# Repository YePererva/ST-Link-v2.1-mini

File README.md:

# ST-Link v2.1 - mini

** Status ** : Unfinished and deprecated due to obtaining the [STLink V3 mini](https://www.st.com/en/development-tools/stlink-v3mini.html)

The idea of this project came, when I broke my [NUCLEO-L432KC](https://www.st.com/content/st_com/en/products/evaluation-tools/product-evaluation-tools/mcu-mpu-eval-tools/stm32-mcu-mpu-eval-tools/stm32-nucleo-boards/nucleo-l432kc.html) board and thought if I can cannibalize the leftovers of it and make a replacement PCB, where I can transplant the microcontroller and keep using the chip from Nucleo board as a dedicated STLink programmer.

This repository has no purpose or instructions for hacking the firmware or any other part of STLink!

Although, the schematic of original [NUCLEO-L432KC](https://www.st.com/resource/en/data_brief/nucleo-l432kc.pdf) and its STLink part is available [on STMicroelectronics website](https://www.st.com/resource/en/schematic_pack/nucleo-32pins_sch.zip) it has few points that I don't like:
- it uses USB-micro, while USB type C seems to be more appropriate
- STMicroelectronics introduced the `STCD-14` connector for STM32 programming (via SWD + VCP). It would be nice to have it
- official firmware allows to switch device between programming the STM32 and STM8 microcontrollers
- the [Black Magic Probe](https://github.com/blacksphere/blackmagic/wiki) is another popular programming / debugging tool and have a [firmware](https://github.com/blacksphere/blackmagic/tree/master/src/platforms/stlink), compatible with STM32F103CxT6 microcontroller. It may be reasonable to have a programming interface to convert this DIY STLink into BMP later in future.
- can't power-up the target microcontroller from STLink.

## What is inside of repository
- `datasheets`: \
  datasheets for microcontroller, USB type Connector, etc.
- `project files`:
  - `simplified`: \
    simplified version of STLink without EDS protection of either USB or SWD / SWIM / VCP
  - `protected`: \
    version with EDS protection
  - `STDC14-adapters`: \
    The STLink V3 mini can't be connected directly to devboards alike BluePill, etc. due to different connector pinout and size. Here are 2 connectors for STDC14 : as breadboard breakout board and as plug-&-play connector to SWD interface on BluePill board.
- `references`: \
    references on stuff like pinout of programming interfaces, STLinks made by other people, etc.

### Similar projects

- https://github.com/MartinD-CZ/ST-Link-V21-clone

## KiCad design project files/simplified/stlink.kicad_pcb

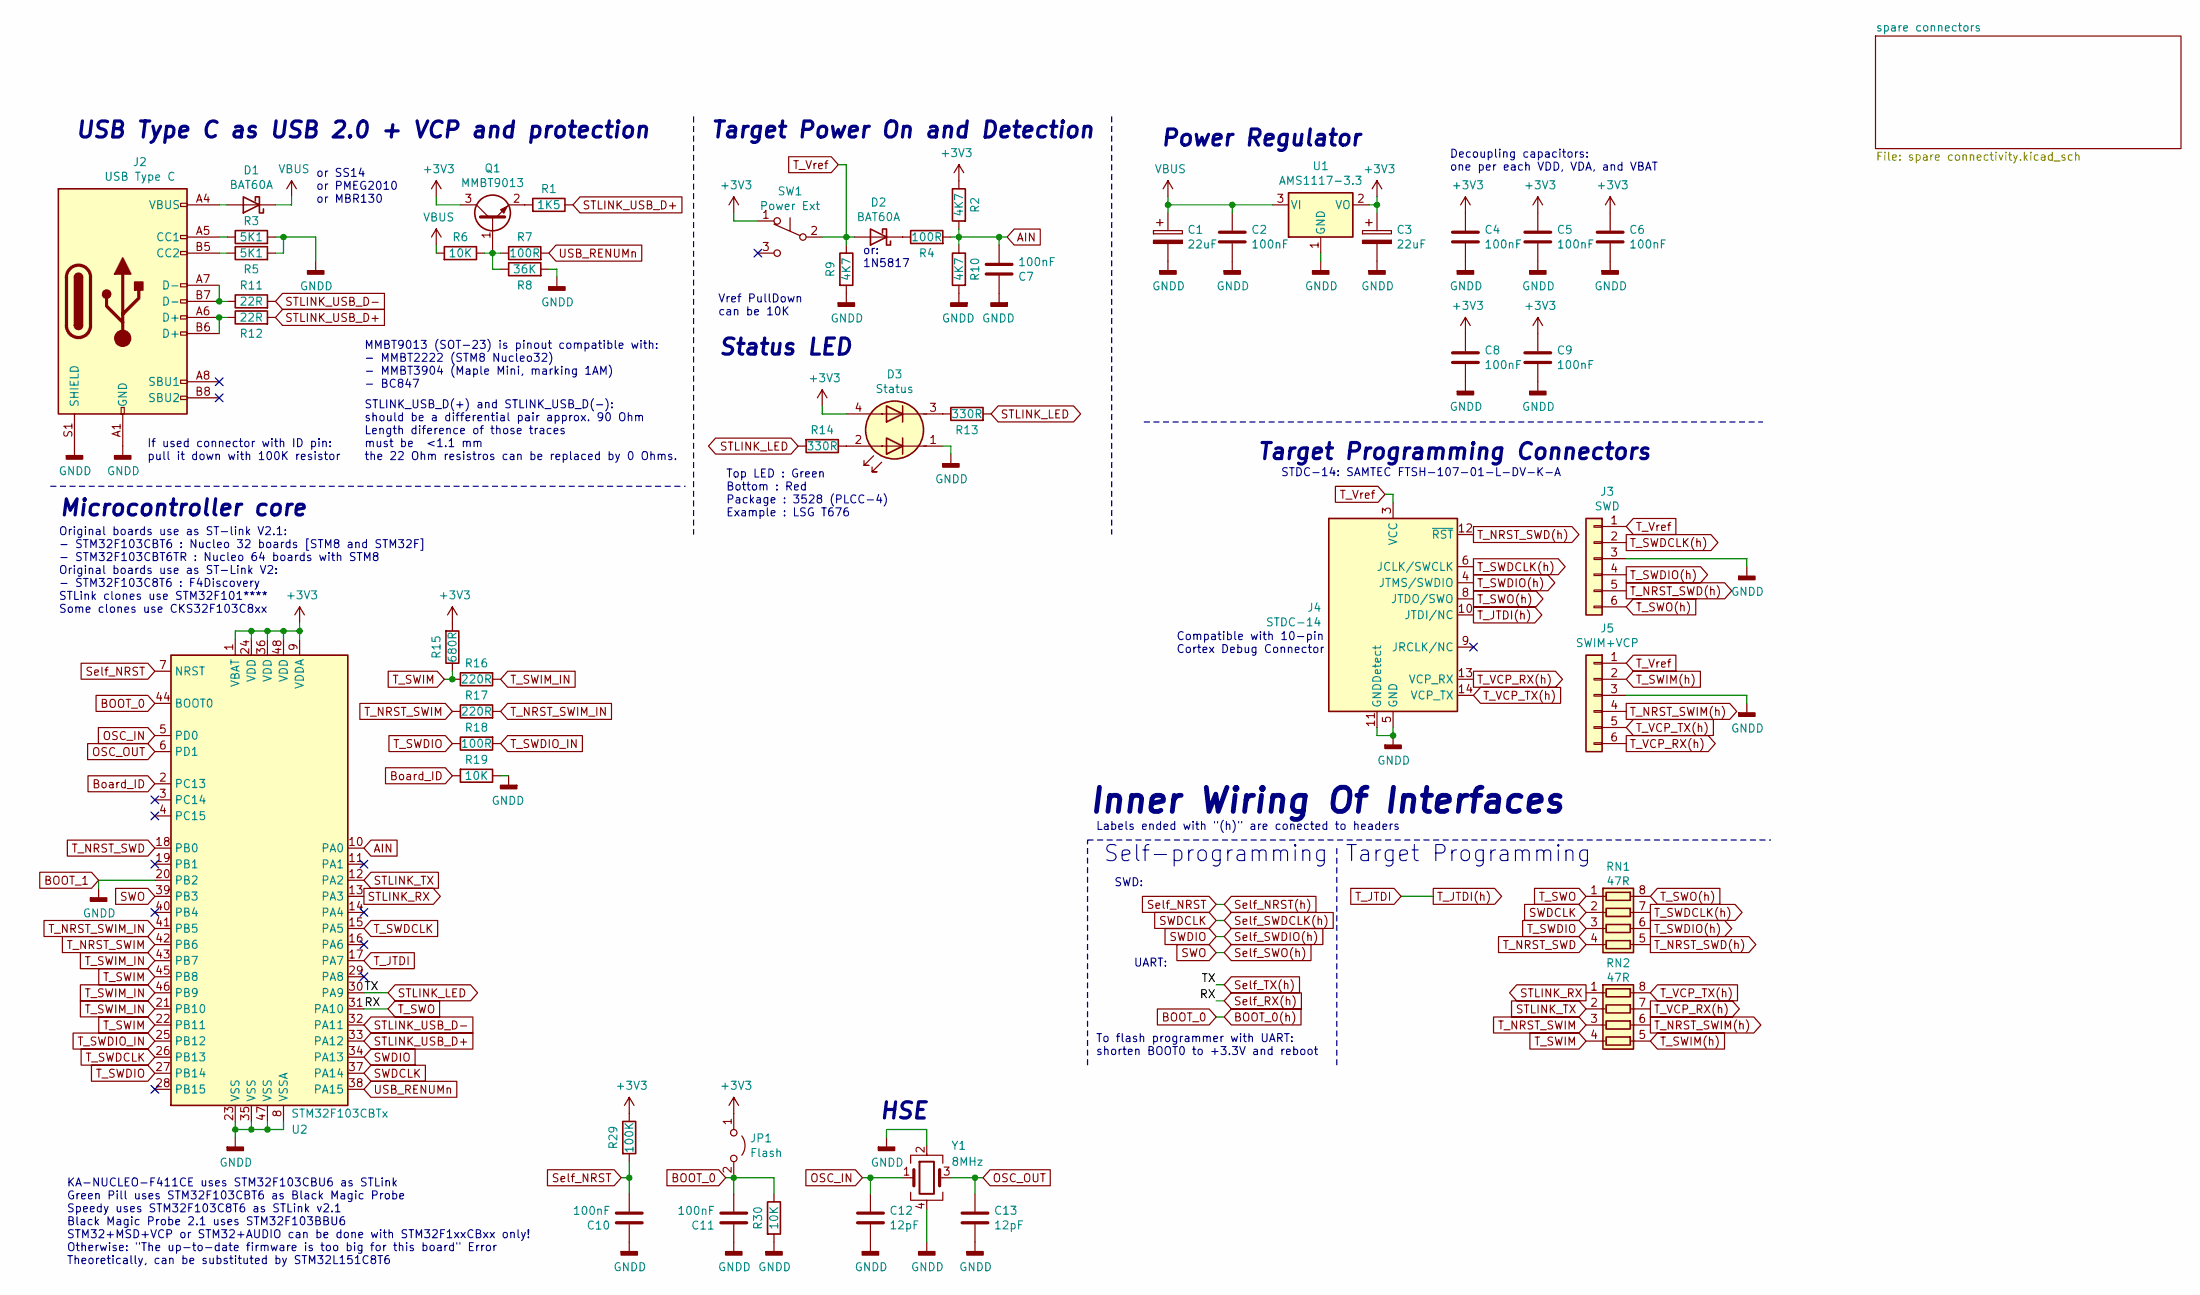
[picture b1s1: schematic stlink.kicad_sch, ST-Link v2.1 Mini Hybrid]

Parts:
C1, C3: 22uF; CP_EIA-7343-30_AVX-N
C2, C4, C5, C6, C7, C8, C9, C10, C11: 100nF; C_0603_1608Metric
C12, C13: 12pF; C_0603_1608Metric
D1, D2: BAT60A; D_SOD-323
D3: Status; LED_Avago_PLCC4_3.2x2.8mm_CW
J2: USB Type C; USB_C_Receptacle_Palconn_UTC16-G
J3: SWD; PinHeader_1x06_P2.54mm_Vertical
J4: STDC-14; PinHeader_2x07_P1.27mm_Vertical_SMD
J5: SWIM+VCP; PinHeader_1x06_P2.54mm_Vertical
JP1: Flash; PinSocket_2x01_P1.27mm_Vertical
Q1: MMBT9013; SOT-23
R1: 1K5; R_0603_1608Metric
R2, R9, R10: 4K7; R_0603_1608Metric
R3, R5: 5K1; R_0603_1608Metric
R4, R7, R18: 100R; R_0603_1608Metric
R6, R19, R30: 10K; R_0603_1608Metric
R8: 36K; R_0603_1608Metric
R11, R12: 22R; R_0603_1608Metric
R13, R14: 330R; R_0603_1608Metric
R15: 680R; R_0603_1608Metric
R16, R17: 220R; R_0603_1608Metric
R29: 100K; R_0603_1608Metric
RN1, RN2: 47R
SW1: Power Ext
U1: AMS1117-3.3; SOT-223-3_TabPin2
U2: STM32F103CBTx; LQFP-48_7x7mm_P0.5mm
Y1: 8MHz; Crystal_SMD_Abracon_ABM8G-4Pin_3.2x2.5mm

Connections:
AIN: C7.2, R2.2, R4.2, R10.1, U2.10 (PA0); also elsewhere on the board
BOOT_0: C11.2, JP1.2 (B), R30.1, U2.44 (BOOT0); also elsewhere on the board
BOOT_1: C1.2, C2.2, C3.2, C4.2, C5.2, C6.2, C7.1, C8.2, C9.2, C10.1, C11.1, C12.2, C13.2, D3.1 (A1), J2.A1 (GND), J2.A12 (GND), J2.B1 (GND), J2.B12 (GND), J2.S1 (SHIELD), J3.3, J4.5 (GND), J4.7 (GND), J4.11 (GNDDetect), J5.3, R3.2, R5.2, R8.2, R9.2, R10.2, R19.1, R30.2, U1.1 (GND), U2.8 (VSSA), U2.20 (PB2), U2.23 (VSS), U2.35 (VSS), U2.47 (VSS), Y1.2, Y1.4; also elsewhere on the board
Board_ID: R19.2, U2.2 (PC13); also elsewhere on the board
unnamed: D1.2 (A), J2.A4 (VBUS), J2.A9 (VBUS), J2.B4 (VBUS), J2.B9 (VBUS)
unnamed: D2.1 (K), R4.1
unnamed: D3.2 (K1), R14.1
unnamed: D3.3 (A2), R13.1
unnamed: J2.A5 (CC1), R3.1
unnamed: J2.A6 (D+), J2.B6 (D+), R12.1
unnamed: J2.A7 (D-), J2.B7 (D-), R11.1
unnamed: J2.B5 (CC2), R5.1
unnamed: Q1.1 (B), R6.1, R7.1, R8.1
unnamed: Q1.2 (E), R1.2
OSC_IN: C12.1, U2.5 (PD0), Y1.1; also elsewhere on the board
OSC_OUT: C13.1, U2.6 (PD1), Y1.3; also elsewhere on the board
STLINK_LED: R13.2, R14.2, U2.30 (PA9); also elsewhere on the board
STLINK_RX: RN2.1 (R1.1), U2.13 (PA3); also elsewhere on the board
STLINK_TX: RN2.2 (R2.1), U2.12 (PA2); also elsewhere on the board
STLINK_USB_D+: R1.1, R12.2, U2.33 (PA12); also elsewhere on the board
STLINK_USB_D-: R11.2, U2.32 (PA11); also elsewhere on the board
SWDCLK: RN1.2 (R2.1), U2.37 (PA14); also elsewhere on the board
SWDIO: U2.34 (PA13); also elsewhere on the board
SWO: U2.39 (PB3); also elsewhere on the board
Self_NRST: C10.2, R29.2, U2.7 (NRST); also elsewhere on the board
Self_RX(h): RN1.1 (R1.1), U2.31 (PA10); also elsewhere on the board
T_JTDI: J4.10 (JTDI/NC), U2.17 (PA7); also elsewhere on the board
T_NRST_SWD: RN1.4 (R4.1), U2.18 (PB0); also elsewhere on the board
T_NRST_SWD(h): J3.5, J4.12 (~RST), RN1.5 (R4.2)
T_NRST_SWIM: R17.1, RN2.3 (R3.1), U2.42 (PB6); also elsewhere on the board
T_NRST_SWIM(h): J5.4, RN2.6 (R3.2)
T_NRST_SWIM_IN: R17.2, U2.41 (PB5); also elsewhere on the board
T_SWDCLK: U2.15 (PA5), U2.26 (PB13); also elsewhere on the board
T_SWDCLK(h): J3.2, J4.6 (JCLK/SWCLK), RN1.7 (R2.2)
T_SWDIO: R18.1, RN1.3 (R3.1), U2.27 (PB14); also elsewhere on the board
T_SWDIO(h): J3.4, J4.4 (JTMS/SWDIO), RN1.6 (R3.2)
T_SWDIO_IN: R18.2, U2.25 (PB12); also elsewhere on the board
T_SWIM: R15.1, R16.1, RN2.4 (R4.1), U2.22 (PB11), U2.45 (PB8); also elsewhere on the board
T_SWIM(h): J5.2, RN2.5 (R4.2)
T_SWIM_IN: R16.2, U2.21 (PB10), U2.43 (PB7), U2.46 (PB9); also elsewhere on the board
T_SWO(h): J3.6, J4.8 (JTDO/SWO), RN1.8 (R1.2)
T_VCP_RX(h): J4.13 (VCP_RX), J5.6, RN2.7 (R2.2)
T_VCP_TX(h): J4.14 (VCP_TX), J5.5, RN2.8 (R1.2)
T_Vref: D2.2 (A), J3.1, J4.3 (VCC), J5.1, R9.1, SW1.2 (B)
USB_RENUMn: R7.2, U2.38 (PA15); also elsewhere on the board
VBUS: C1.1, C2.1, D1.1 (K), R6.2, U1.3 (VI)

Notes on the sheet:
Microcontroller core
Original boards use as ST-link V2.1: - STM32F103CBT6 : Nucleo 32 boards [STM8 and STM32F] - STM32F103CBT6TR : Nucleo 64 boards with STM8 Original boards use as ST-Link V2: - STM32F103C8T6 : F4Discovery STLink clones use STM32F101**** Some clones use CKS32F103C8xx
KA-NUCLEO-F411CE uses STM32F103CBU6 as STLink Green Pill uses STM32F103CBT6 as Black Magic Probe Speedy uses STM32F103C8T6 as STLink v2.1 Black Magic Probe 2.1 uses STM32F103BBU6 STM32+MSD+VCP or STM32+AUDIO can be done with STM32F1xxCBxx only! Otherwise: "The up-to-date firmware is too big for thi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
USB Type C as USB 2.0 + VCP and protection
If used connector with ID pin: pull it down with 100K resistor
or SS14 or PMEG2010 or MBR130
MMBT9013 (SOT-23) is pinout compatible with: - MMBT2222 (STM8 Nucleo32) - MMBT3904 (Maple Mini, marking 1AM) - BC847
STLINK_USB_D(+) and STLINK_USB_D(-): should be a differential pair approx. 90 Ohm Length diference of those traces must be <1.1 mm the 22 Ohm resistros can be replaced by 0 Ohms.
Target Power On and Detection
Vref PullDown can be 10K
Status LED
Top LED : Green Bottom : Red Package : 3528 (PLCC-4) Example : LSG T676
or: 1N5817
HSE
Inner Wiring Of Interfaces
Labels ended with "(h)" are conected to headers
To flash programmer with UART: shorten BOOT0 to +3.3V and reboot
SWD:
Power Regulator
UART:
Compatible with 10-pin Cortex Debug Connector
Target Programming Connectors
STDC-14: SAMTEC FTSH-107-01-L-DV-K-A
Self-programming
Target Programming
Decoupling capacitors: one per each VDD, VDA, and VBAT

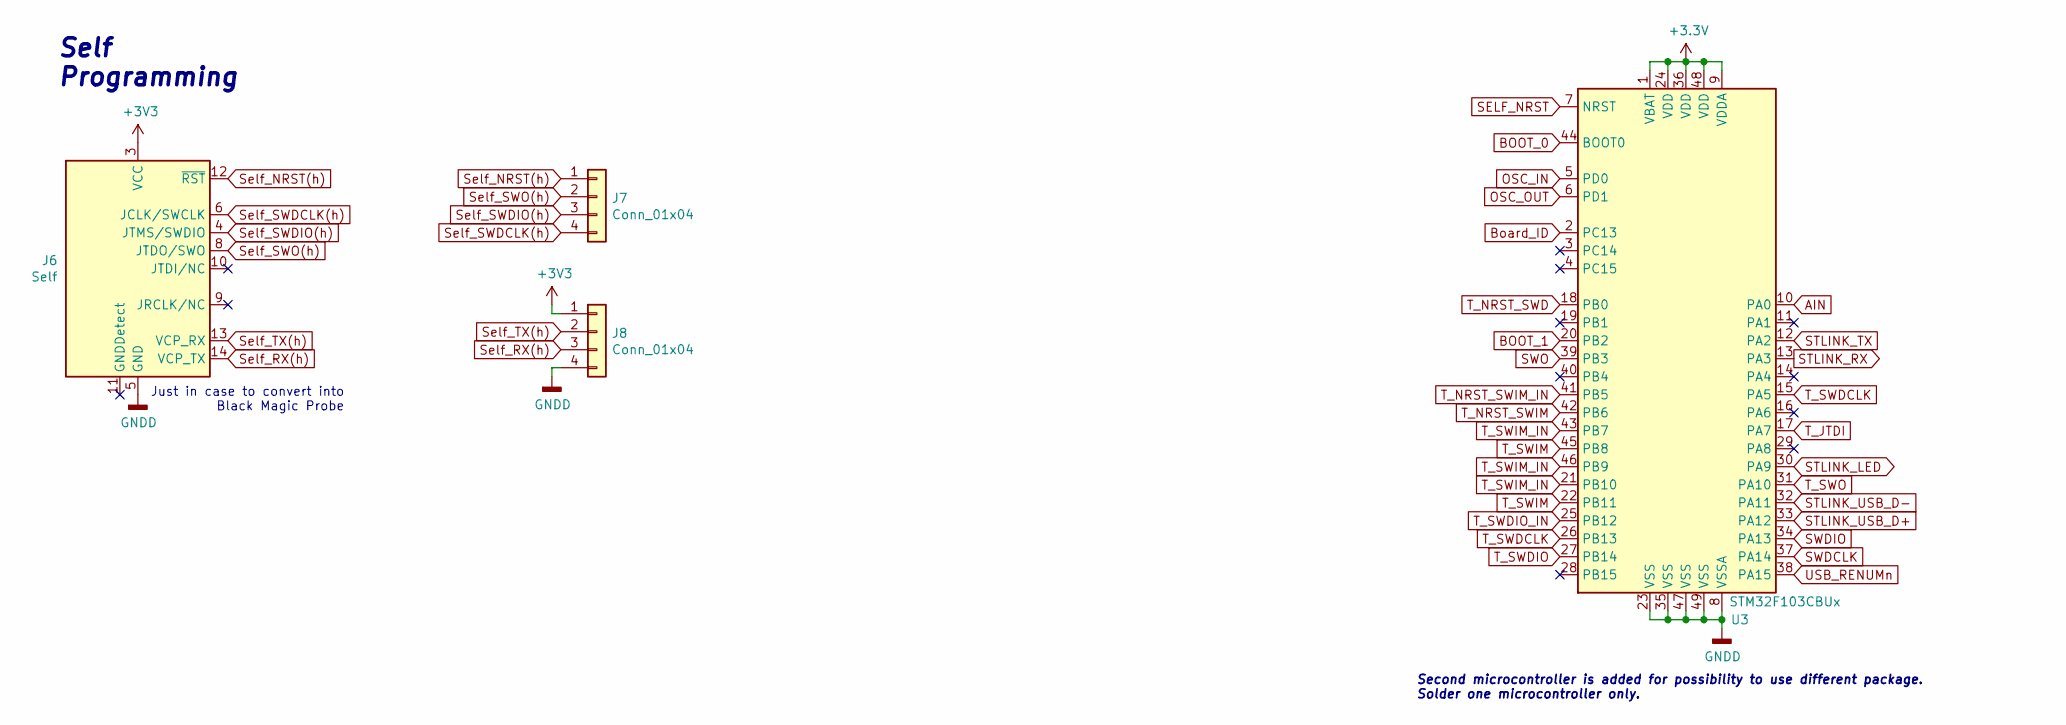
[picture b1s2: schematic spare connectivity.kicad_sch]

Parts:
J6: Self; PinHeader_2x07_P1.27mm_Vertical_SMD
J7, J8: Conn_01x04; PinHeader_1x04_P2.54mm_Vertical
U3: STM32F103CBUx; QFN-48-1EP_7x7mm_P0.5mm_EP5.6x5.6mm

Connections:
AIN: U3.10 (PA0); also elsewhere on the board
BOOT_0: U3.44 (BOOT0); also elsewhere on the board
BOOT_1: J6.5 (GND), J6.7 (GND), J8.4, U3.8 (VSSA), U3.20 (PB2), U3.23 (VSS), U3.35 (VSS), U3.47 (VSS), U3.49 (VSS); also elsewhere on the board
Board_ID: U3.2 (PC13); also elsewhere on the board
OSC_IN: U3.5 (PD0); also elsewhere on the board
OSC_OUT: U3.6 (PD1); also elsewhere on the board
SELF_NRST: U3.7 (NRST)
STLINK_LED: J6.13 (VCP_RX), J8.2, U3.30 (PA9); also elsewhere on the board
STLINK_RX: U3.13 (PA3); also elsewhere on the board
STLINK_TX: U3.12 (PA2); also elsewhere on the board
STLINK_USB_D+: U3.33 (PA12); also elsewhere on the board
STLINK_USB_D-: U3.32 (PA11); also elsewhere on the board
SWDCLK: J6.6 (JCLK/SWCLK), J7.4, U3.37 (PA14); also elsewhere on the board
SWDIO: J6.4 (JTMS/SWDIO), J7.3, U3.34 (PA13); also elsewhere on the board
SWO: J6.8 (JTDO/SWO), J7.2, U3.39 (PB3); also elsewhere on the board
Self_NRST: J6.12 (~RST), J7.1; also elsewhere on the board
Self_RX(h): J6.14 (VCP_TX), J8.3, U3.31 (PA10); also elsewhere on the board
T_JTDI: U3.17 (PA7); also elsewhere on the board
T_NRST_SWD: U3.18 (PB0); also elsewhere on the board
T_NRST_SWIM: U3.42 (PB6); also elsewhere on the board
T_NRST_SWIM_IN: U3.41 (PB5); also elsewhere on the board
T_SWDCLK: U3.15 (PA5), U3.26 (PB13); also elsewhere on the board
T_SWDIO: U3.27 (PB14); also elsewhere on the board
T_SWDIO_IN: U3.25 (PB12); also elsewhere on the board
T_SWIM: U3.22 (PB11), U3.45 (PB8); also elsewhere on the board
T_SWIM_IN: U3.21 (PB10), U3.43 (PB7), U3.46 (PB9); also elsewhere on the board
USB_RENUMn: U3.38 (PA15); also elsewhere on the board

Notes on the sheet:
Self Programming
Just in case to convert into Black Magic Probe
Second microcontroller is added for possibility to use different package. Solder one microcontroller only.

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
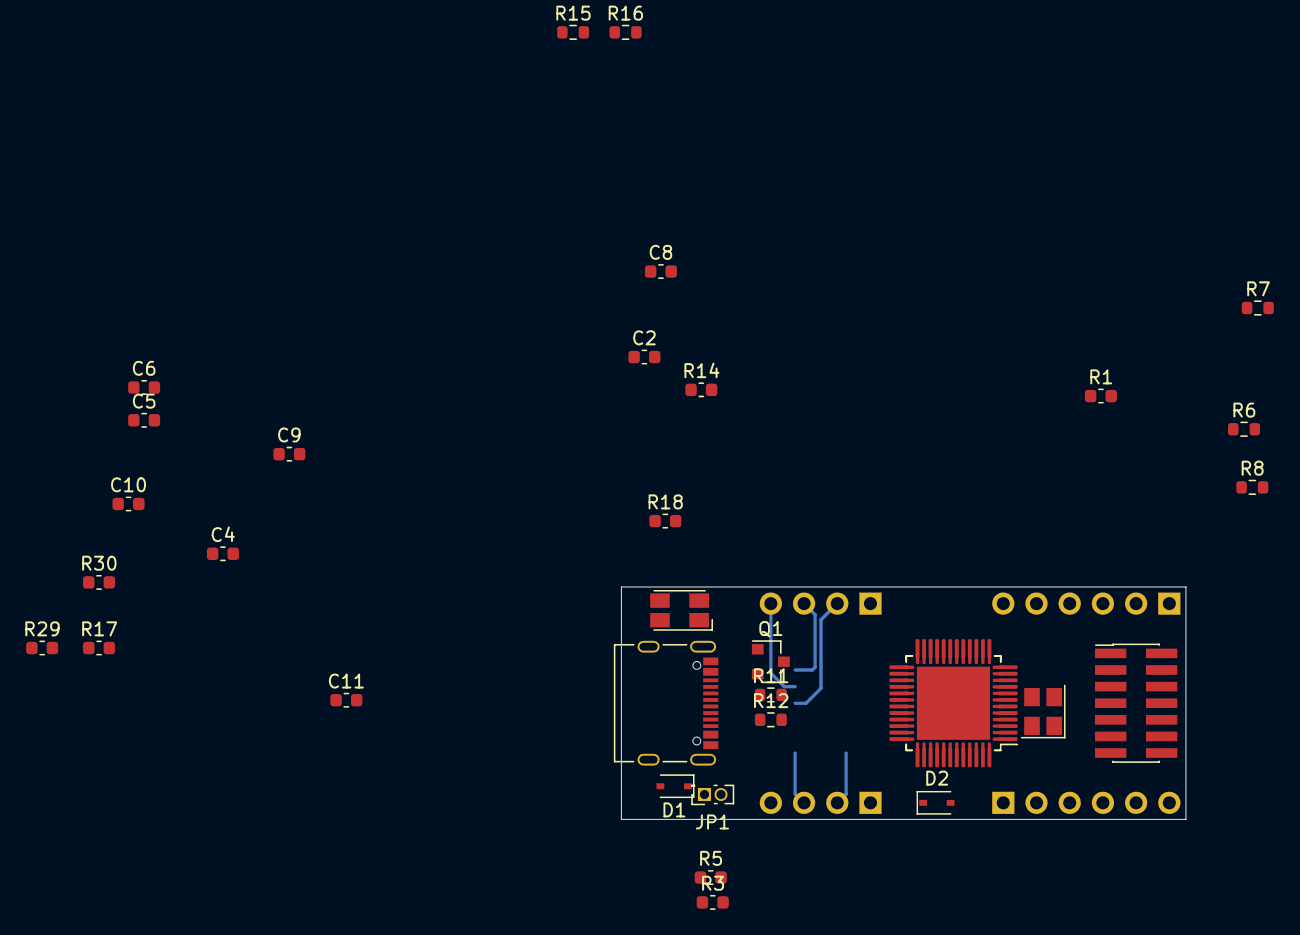
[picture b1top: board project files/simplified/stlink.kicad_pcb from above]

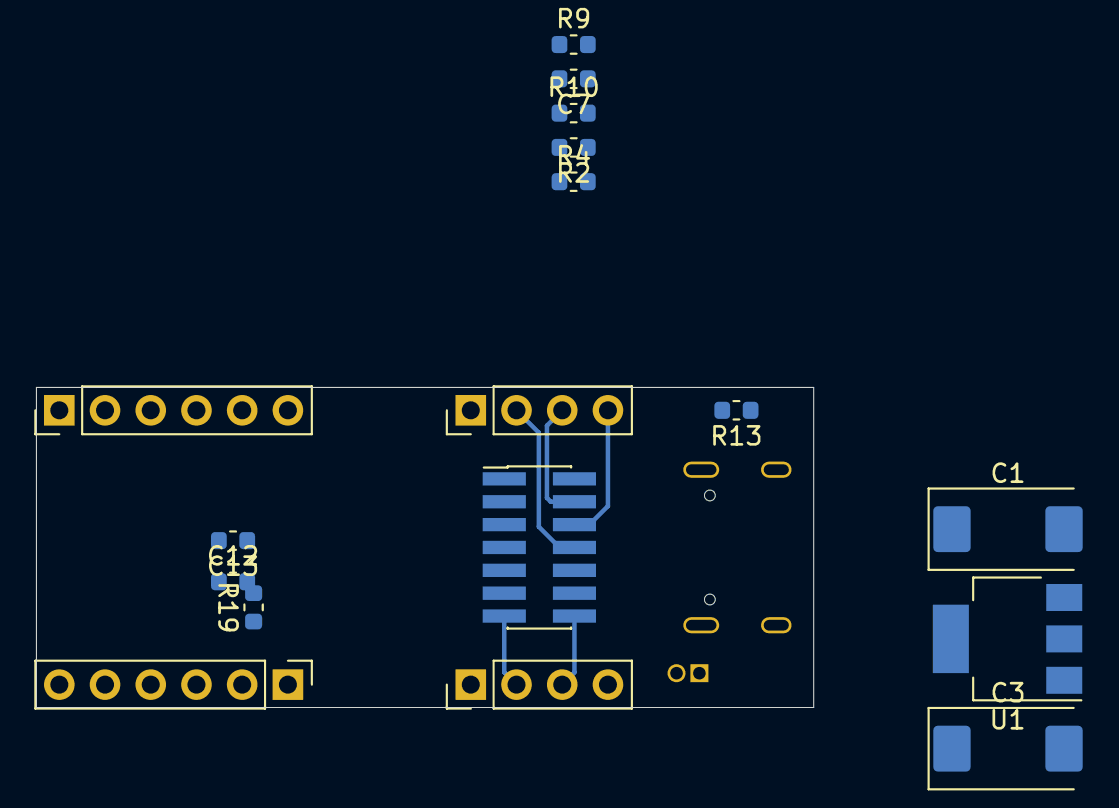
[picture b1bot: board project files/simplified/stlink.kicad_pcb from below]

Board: 2 copper layers, 43.2 x 17.8 mm, 50 parts (17 on the bottom side), 45 nets.

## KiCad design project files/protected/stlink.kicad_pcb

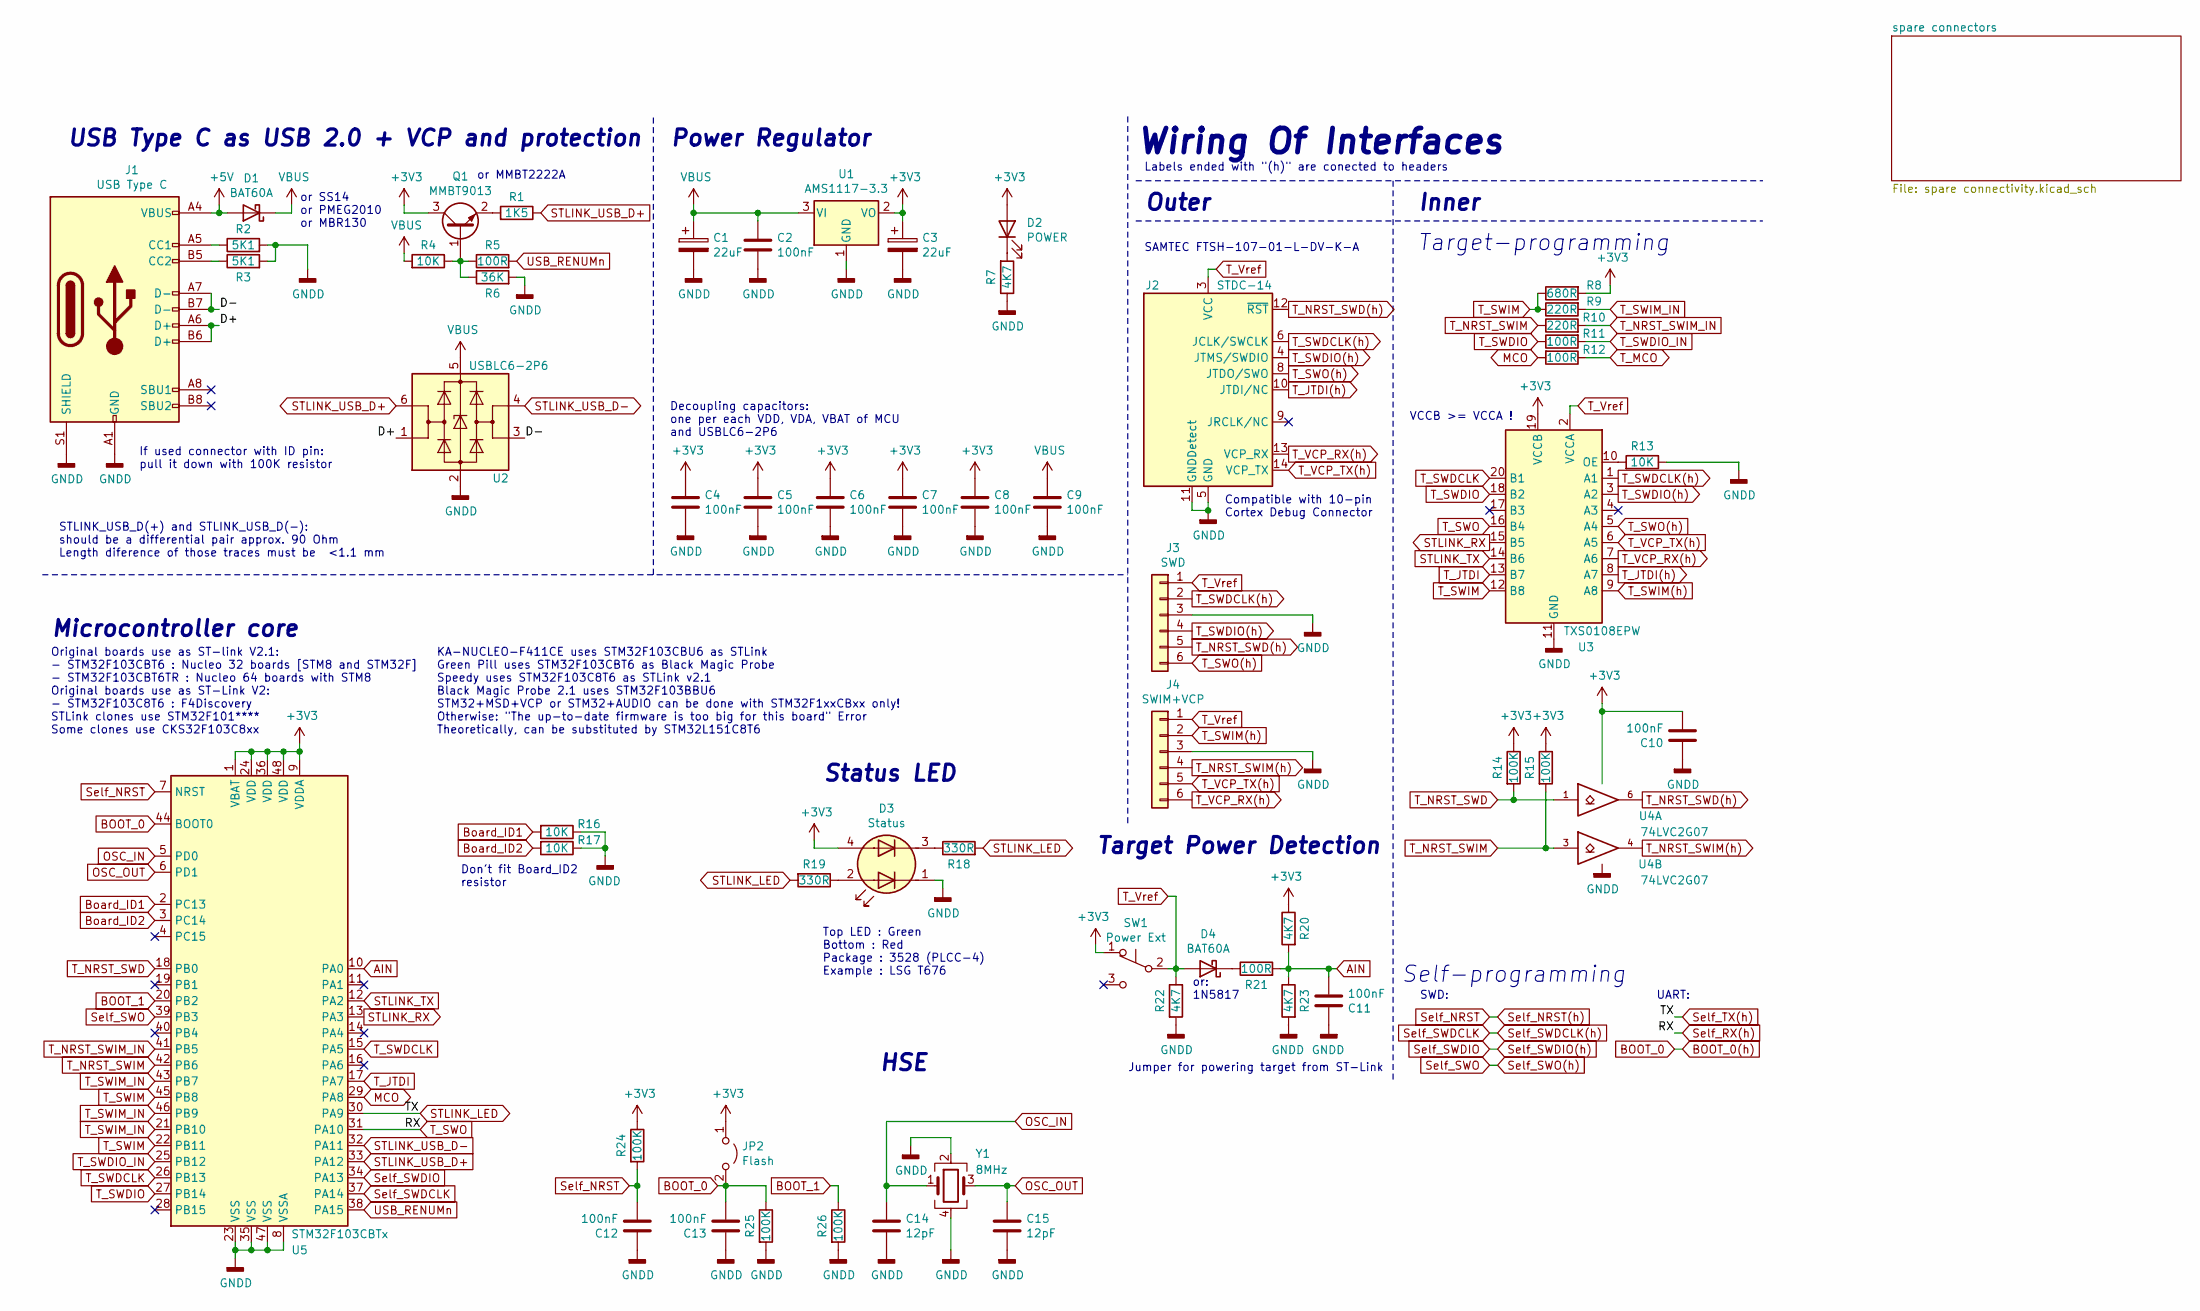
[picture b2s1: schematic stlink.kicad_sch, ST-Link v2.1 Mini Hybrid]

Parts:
C1, C3: 22uF; CP_EIA-7343-30_AVX-N
C2, C4, C5, C6, C7, C8, C9, C10, C11, C12, C13: 100nF; C_0603_1608Metric
C14, C15: 12pF; C_0603_1608Metric
D1, D4: BAT60A; D_SOD-323
D2: POWER; LED_0805_2012Metric_Castellated
D3: Status; LED_Avago_PLCC4_3.2x2.8mm_CW
J1: USB Type C; USB_C_Receptacle_Palconn_UTC16-G
J2: STDC-14; PinHeader_2x07_P1.27mm_Vertical_SMD
J3: SWD; PinHeader_1x06_P2.54mm_Vertical
J4: SWIM+VCP; PinHeader_1x06_P2.54mm_Vertical
JP2: Flash; PinSocket_2x01_P1.27mm_Vertical
Q1: MMBT9013; SOT-23
R1: 1K5; R_0603_1608Metric
R2, R3: 5K1; R_0603_1608Metric
R4, R13, R16, R17: 10K; R_0603_1608Metric
R5, R11, R12, R21: 100R; R_0603_1608Metric
R6: 36K; R_0603_1608Metric
R7, R20, R22, R23: 4K7; R_0603_1608Metric
R8: 680R; R_0603_1608Metric
R9, R10: 220R; R_0603_1608Metric
R14, R15, R24, R25, R26: 100K; R_0603_1608Metric
R18, R19: 330R; R_0603_1608Metric
SW1: Power Ext; SW_SPDT_PCM12
U1: AMS1117-3.3; SOT-223-3_TabPin2
U2: USBLC6-2P6; SOT-666
U3: TXS0108EPW; TSSOP-20_4.4x6.5mm_P0.65mm
U4: 74LVC2G07; SOT-363_SC-70-6
U5: STM32F103CBTx; LQFP-48_7x7mm_P0.5mm
Y1: 8MHz; Crystal_SMD_Abracon_ABM8G-4Pin_3.2x2.5mm

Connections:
+5V: D1.2 (A), J1.A4 (VBUS), J1.A9 (VBUS), J1.B4 (VBUS), J1.B9 (VBUS)
/D+: J1.A6 (D+), J1.B6 (D+), U2.1 (I/O1)
/D-: J1.A7 (D-), J1.B7 (D-), U2.3 (I/O2)
AIN: C11.2, R20.2, R21.2, R23.1, U5.10 (PA0); also elsewhere on the board
BOOT_0: C13.2, JP2.2 (B), R25.1, U5.44 (BOOT0); also elsewhere on the board
BOOT_1: R26.1, U5.20 (PB2); also elsewhere on the board
Board_ID1: R16.2, U5.2 (PC13); also elsewhere on the board
Board_ID2: R17.2, U5.3 (PC14); also elsewhere on the board
GND: C1.2, C2.2, C3.2, C4.2, C5.2, C6.2, C7.2, C8.2, C9.2, C10.1, C11.1, C12.1, C13.1, C14.2, C15.2, D3.1 (A1), J1.A1 (GND), J1.A12 (GND), J1.B1 (GND), J1.B12 (GND), J1.S1 (SHIELD), J2.5 (GND), J2.7 (GND), J2.11 (GNDDetect), J3.3, J4.3, R2.2, R3.2, R6.2, R7.1, R13.1, R16.1, R17.1, R22.2, R23.2, R25.2, R26.2, U1.1 (GND), U2.2 (GND), U3.11 (GND), U4.2 (GND), U5.8 (VSSA), U5.23 (VSS), U5.35 (VSS), U5.47 (VSS), Y1.2, Y1.4; also elsewhere on the board
MCO: R12.2, U5.29 (PA8); also elsewhere on the board
unnamed: D2.1 (K), R7.2
unnamed: D3.2 (K1), R19.1
unnamed: D3.3 (A2), R18.1
unnamed: D4.1 (K), R21.1
unnamed: J1.A5 (CC1), R2.1
unnamed: J1.B5 (CC2), R3.1
unnamed: Q1.1 (B), R4.1, R5.1, R6.1
unnamed: Q1.2 (E), R1.2
unnamed: R13.2, U3.10 (OE)
OSC_IN: C14.1, U5.5 (PD0), Y1.1; also elsewhere on the board
OSC_OUT: C15.1, U5.6 (PD1), Y1.3; also elsewhere on the board
STLINK_LED: R18.2, R19.2, U5.30 (PA9); also elsewhere on the board
STLINK_RX: U3.15 (B5), U5.13 (PA3); also elsewhere on the board
STLINK_TX: U3.14 (B6), U5.12 (PA2); also elsewhere on the board
STLINK_USB_D+: R1.1, U2.6 (I/O1), U5.33 (PA12); also elsewhere on the board
STLINK_USB_D-: U2.4 (I/O2), U5.32 (PA11); also elsewhere on the board
Self_NRST: C12.2, R24.2, U5.7 (NRST); also elsewhere on the board
Self_RX(h): U3.16 (B4), U5.31 (PA10); also elsewhere on the board
Self_SWDCLK: U5.37 (PA14); also elsewhere on the board
Self_SWDIO: U5.34 (PA13); also elsewhere on the board
Self_SWO: U5.39 (PB3); also elsewhere on the board
T_JTDI: U3.13 (B7), U5.17 (PA7); also elsewhere on the board
T_JTDI(h): J2.10 (JTDI/NC), U3.8 (A7)
T_MCO: R12.1
T_NRST_SWD: R14.2, U4.1, U5.18 (PB0); also elsewhere on the board
T_NRST_SWD(h): J2.12 (~RST), J3.5, U4.6
T_NRST_SWIM: R10.1, R15.2, U4.3, U5.42 (PB6); also elsewhere on the board
T_NRST_SWIM(h): J4.4, U4.4
T_NRST_SWIM_IN: R10.2, U5.41 (PB5); also elsewhere on the board
T_SWDCLK: U3.20 (B1), U5.15 (PA5), U5.26 (PB13); also elsewhere on the board
T_SWDCLK(h): J2.6 (JCLK/SWCLK), J3.2, U3.1 (A1)
T_SWDIO: R11.1, U3.18 (B2), U5.27 (PB14); also elsewhere on the board
T_SWDIO(h): J2.4 (JTMS/SWDIO), J3.4, U3.3 (A2)
T_SWDIO_IN: R11.2, U5.25 (PB12); also elsewhere on the board
T_SWIM: R8.1, R9.1, U3.12 (B8), U5.22 (PB11), U5.45 (PB8); also elsewhere on the board
T_SWIM(h): J4.2, U3.9 (A8)
T_SWIM_IN: R9.2, U5.21 (PB10), U5.43 (PB7), U5.46 (PB9); also elsewhere on the board
T_SWO(h): J2.8 (JTDO/SWO), J3.6, U3.5 (A4)
T_VCP_RX(h): J2.13 (VCP_RX), J4.6, U3.7 (A6)
T_VCP_TX(h): J2.14 (VCP_TX), J4.5, U3.6 (A5)
T_Vref: D4.2 (A), J2.3 (VCC), J3.1, J4.1, R22.1, SW1.2 (B), U3.2 (VCCA)
USB_RENUMn: R5.2, U5.38 (PA15); also elsewhere on the board
VBUS: C1.1, C2.1, C9.1, D1.1 (K), R4.2, U1.3 (VI), U2.5 (VBUS)

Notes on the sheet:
Microcontroller core
Original boards use as ST-link V2.1: - STM32F103CBT6 : Nucleo 32 boards [STM8 and STM32F] - STM32F103CBT6TR : Nucleo 64 boards with STM8 Original boards use as ST-Link V2: - STM32F103C8T6 : F4Discovery STLink clones use STM32F101**** Some clones use CKS32F103C8xx
STLINK_USB_D(+) and STLINK_USB_D(-): should be a differential pair approx. 90 Ohm Length diference of those traces must be <1.1 mm
USB Type C as USB 2.0 + VCP and protection
If used connector with ID pin: pull it down with 100K resistor
or SS14 or PMEG2010 or MBR130
KA-NUCLEO-F411CE uses STM32F103CBU6 as STLink Green Pill uses STM32F103CBT6 as Black Magic Probe Speedy uses STM32F103C8T6 as STLink v2.1 Black Magic Probe 2.1 uses STM32F103BBU6 STM32+MSD+VCP or STM32+AUDIO can be done with STM32F1xxCBxx only! Otherwise: "The up-to-date firmware is too big for thi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
Don't fit Board_ID2 resistor
or MMBT2222A
Power Regulator
Decoupling capacitors: one per each VDD, VDA, VBAT of MCU and USBLC6-2P6
Status LED
Top LED : Green Bottom : Red Package : 3528 (PLCC-4) Example : LSG T676
HSE
Target Power Detection
Jumper for powering target from ST-Link
Wiring Of Interfaces
Labels ended with "(h)" are conected to headers
Outer
SAMTEC FTSH-107-01-L-DV-K-A
or: 1N5817
Compatible with 10-pin Cortex Debug Connector
Self-programming
VCCB >= VCCA !
Inner
Target-programming
SWD:
UART:

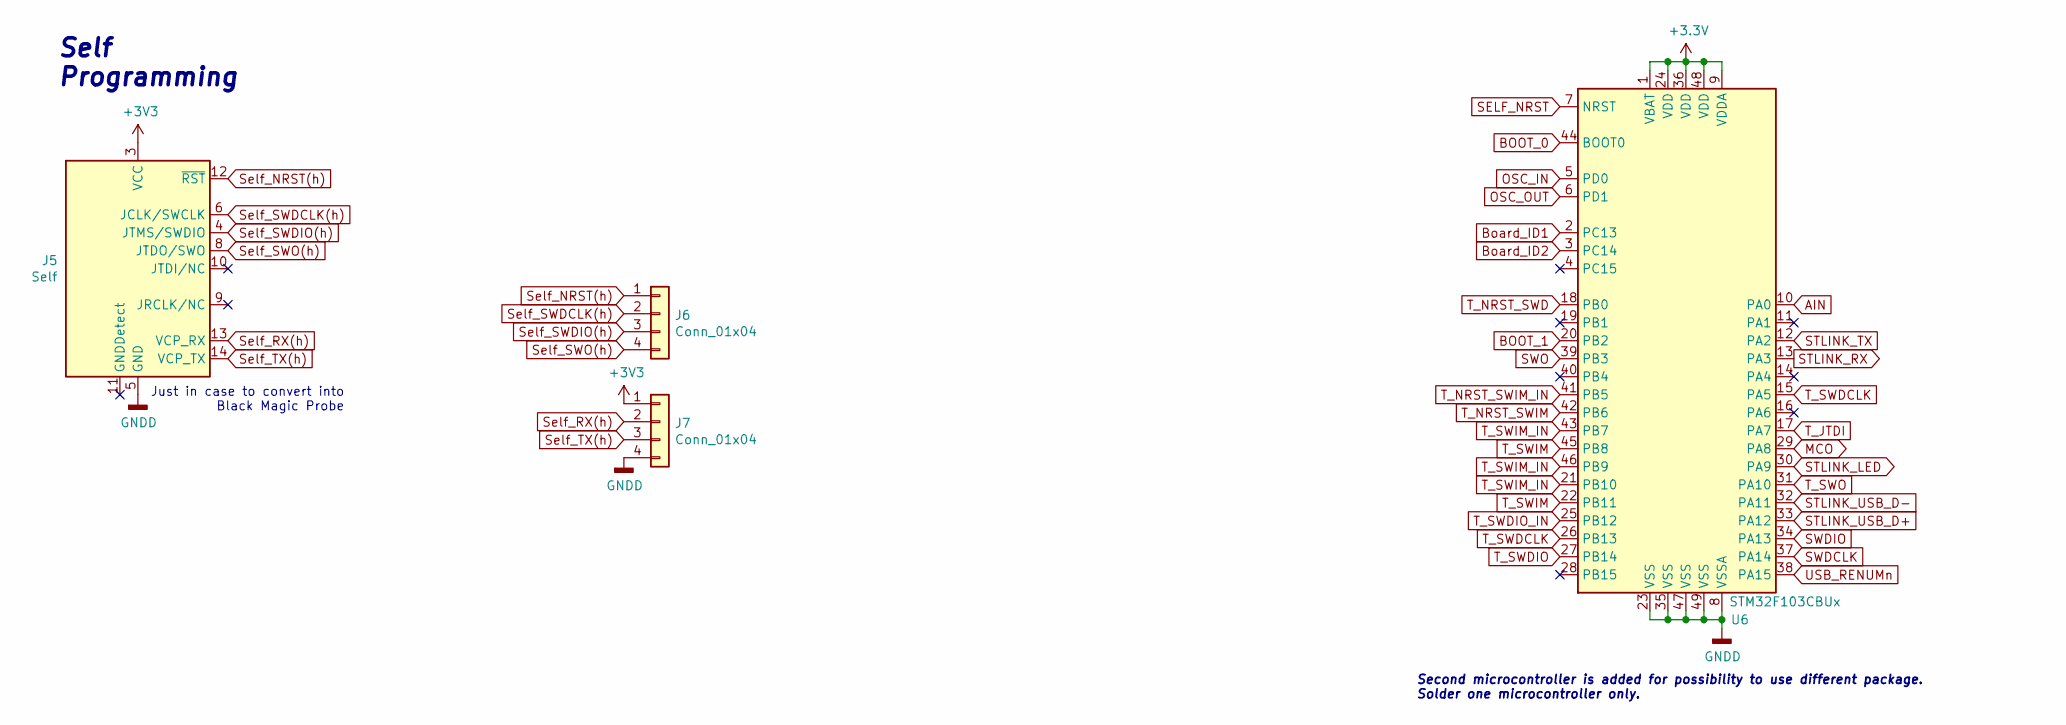
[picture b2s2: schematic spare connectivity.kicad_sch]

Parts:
J5: Self; PinHeader_2x07_P1.27mm_Vertical_SMD
J6, J7: Conn_01x04; PinSocket_1x04_P2.54mm_Vertical
U6: STM32F103CBUx; QFN-48-1EP_7x7mm_P0.5mm_EP5.6x5.6mm

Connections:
AIN: U6.10 (PA0); also elsewhere on the board
BOOT_0: U6.44 (BOOT0); also elsewhere on the board
BOOT_1: U6.20 (PB2); also elsewhere on the board
Board_ID1: U6.2 (PC13); also elsewhere on the board
Board_ID2: U6.3 (PC14); also elsewhere on the board
GND: J5.5 (GND), J5.7 (GND), J7.4, U6.8 (VSSA), U6.23 (VSS), U6.35 (VSS), U6.47 (VSS), U6.49 (VSS); also elsewhere on the board
MCO: U6.29 (PA8); also elsewhere on the board
OSC_IN: U6.5 (PD0); also elsewhere on the board
OSC_OUT: U6.6 (PD1); also elsewhere on the board
SELF_NRST: U6.7 (NRST)
STLINK_LED: J5.14 (VCP_TX), J7.3, U6.30 (PA9); also elsewhere on the board
STLINK_RX: U6.13 (PA3); also elsewhere on the board
STLINK_TX: U6.12 (PA2); also elsewhere on the board
STLINK_USB_D+: U6.33 (PA12); also elsewhere on the board
STLINK_USB_D-: U6.32 (PA11); also elsewhere on the board
SWDCLK: U6.37 (PA14)
SWDIO: U6.34 (PA13)
SWO: U6.39 (PB3)
Self_NRST: J5.12 (~RST), J6.1; also elsewhere on the board
Self_RX(h): J5.13 (VCP_RX), J7.2, U6.31 (PA10); also elsewhere on the board
Self_SWDCLK: J5.6 (JCLK/SWCLK), J6.2; also elsewhere on the board
Self_SWDIO: J5.4 (JTMS/SWDIO), J6.3; also elsewhere on the board
Self_SWO: J5.8 (JTDO/SWO), J6.4; also elsewhere on the board
T_JTDI: U6.17 (PA7); also elsewhere on the board
T_NRST_SWD: U6.18 (PB0); also elsewhere on the board
T_NRST_SWIM: U6.42 (PB6); also elsewhere on the board
T_NRST_SWIM_IN: U6.41 (PB5); also elsewhere on the board
T_SWDCLK: U6.15 (PA5), U6.26 (PB13); also elsewhere on the board
T_SWDIO: U6.27 (PB14); also elsewhere on the board
T_SWDIO_IN: U6.25 (PB12); also elsewhere on the board
T_SWIM: U6.22 (PB11), U6.45 (PB8); also elsewhere on the board
T_SWIM_IN: U6.21 (PB10), U6.43 (PB7), U6.46 (PB9); also elsewhere on the board
USB_RENUMn: U6.38 (PA15); also elsewhere on the board

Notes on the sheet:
Self Programming
Just in case to convert into Black Magic Probe
Second microcontroller is added for possibility to use different package. Solder one microcontroller only.

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
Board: 2 copper layers, 62 parts (19 on the bottom side), 53 nets, no tracks yet.

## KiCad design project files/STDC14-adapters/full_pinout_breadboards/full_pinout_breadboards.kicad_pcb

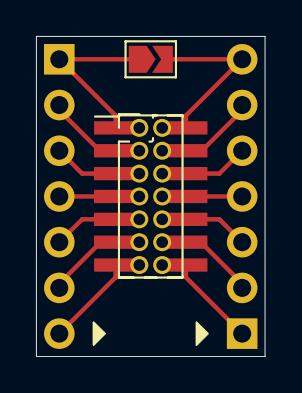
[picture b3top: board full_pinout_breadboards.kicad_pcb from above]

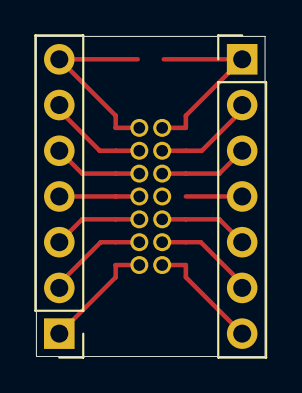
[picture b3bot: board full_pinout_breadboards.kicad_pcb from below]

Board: 2 copper layers, 12.7 x 17.8 mm, 5 parts (2 on the bottom side), 13 nets.

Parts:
J1: STDC14_SMD; PinHeader_2x07_P1.27mm_Vertical_SMD
J2: STDC14_THT; PinHeader_2x07_P1.27mm_Vertical
J3: 1; PinHeader_1x07_P2.54mm_Vertical
J4: 2; PinHeader_1x07_P2.54mm_Vertical
JP1: Reserved; SolderJumper-2_P1.3mm_Open_TrianglePad1.0x1.5mm

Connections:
GND: J1.5, J1.7, J2.5, J2.7, J3.3, J3.4
GND_detect: J1.11, J2.11, J3.6
JCLK_SWDCLK: J1.6, J2.6, J4.5
JRCLK_NC: J1.9, J2.9, J3.5
JTDI_NC: J1.10, J2.10, J4.3
JTDO_SWO: J1.8, J2.8, J4.4
JTMS_SWDIO: J1.4, J2.4, J4.6
NRST: J1.12, J2.12, J4.2
unnamed: J1.1, J2.1, J3.1
unnamed: J1.2, J2.2, J4.7
RX: J1.13, J2.13, J3.7
TX: J1.14, J2.14, J4.1
Vref: J1.3, J2.3, J3.2

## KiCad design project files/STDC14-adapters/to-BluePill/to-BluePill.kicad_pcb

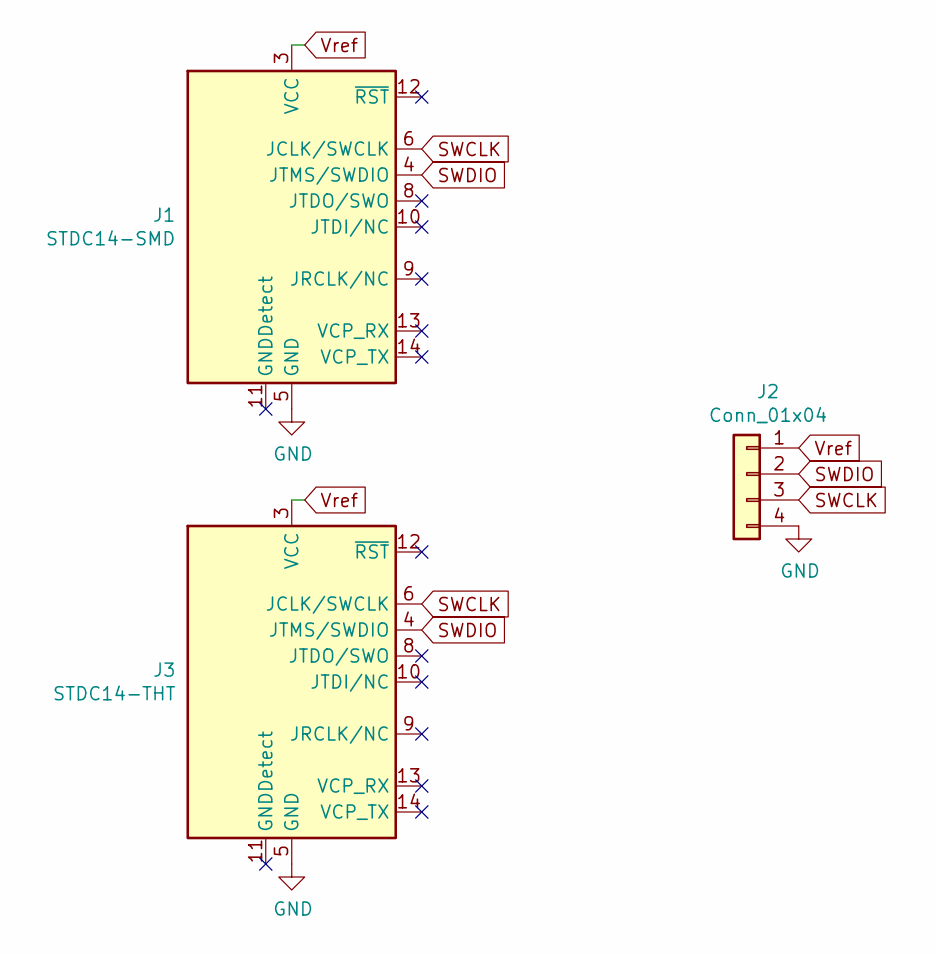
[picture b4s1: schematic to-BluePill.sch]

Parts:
J1: STDC14-SMD; PinHeader_2x07_P1.27mm_Vertical_SMD
J2: Conn_01x04; PinSocket_1x04_P2.54mm_Horizontal
J3: STDC14-THT; PinHeader_2x07_P1.27mm_Vertical

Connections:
GND: J1.5 (GND), J1.7 (GND), J2.4, J3.5 (GND), J3.7 (GND)
SWCLK: J1.6 (JCLK/SWCLK), J2.3, J3.6 (JCLK/SWCLK)
SWDIO: J1.4 (JTMS/SWDIO), J2.2, J3.4 (JTMS/SWDIO)
Vref: J1.3 (VCC), J2.1, J3.3 (VCC)

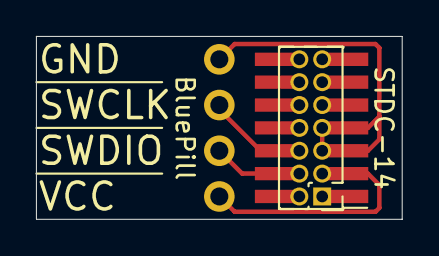
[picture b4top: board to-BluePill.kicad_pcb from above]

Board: 2 copper layers, 20.3 x 10.2 mm, 3 parts (1 on the bottom side), 4 nets.
